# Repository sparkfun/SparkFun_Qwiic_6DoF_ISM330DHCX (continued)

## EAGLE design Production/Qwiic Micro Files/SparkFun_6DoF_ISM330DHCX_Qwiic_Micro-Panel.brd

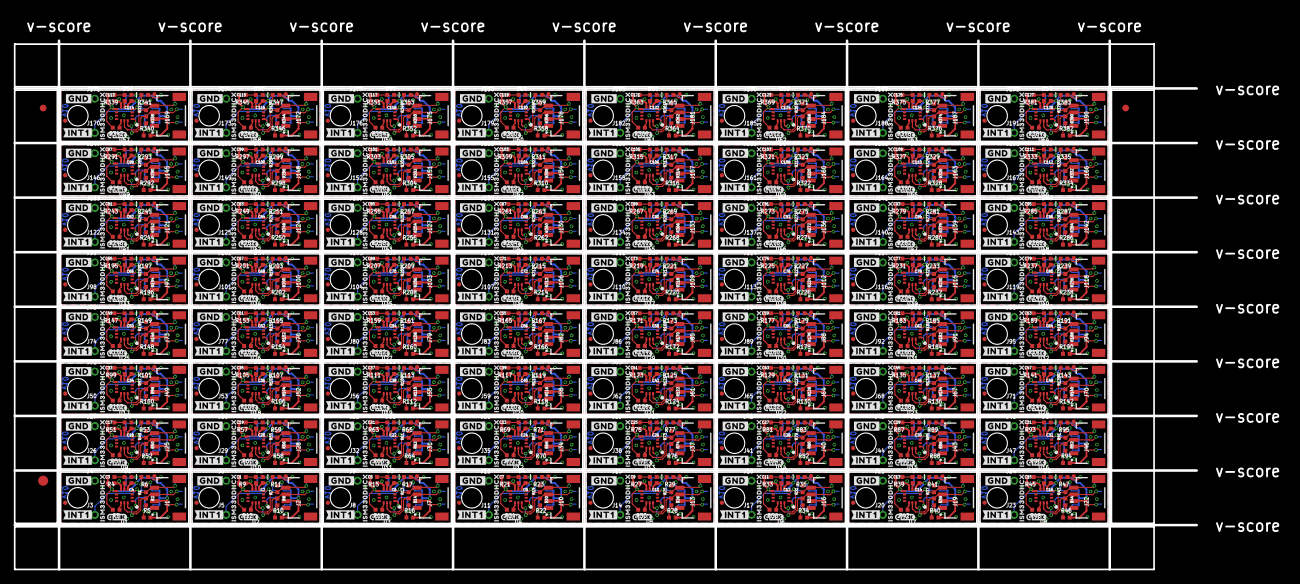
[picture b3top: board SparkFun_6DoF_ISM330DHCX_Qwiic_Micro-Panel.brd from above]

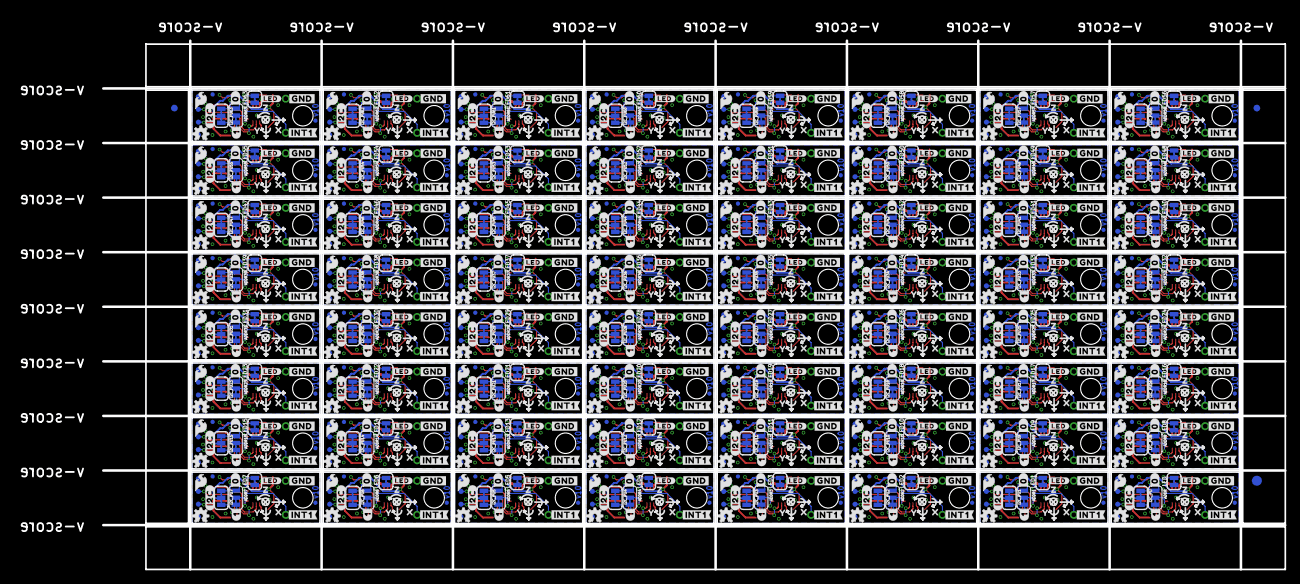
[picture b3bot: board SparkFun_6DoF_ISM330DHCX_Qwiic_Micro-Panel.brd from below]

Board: 2 copper layers, 176.0 x 78.7 mm, 2630 parts (1283 on the bottom side), 832 nets.

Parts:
ADDR, ADDR1, ADDR2, ADDR3, ADDR4, ADDR5, ADDR6, ADDR7, ADDR8, ADDR9, ADDR10, ADDR11, ADDR12, ADDR13, ADDR14, ADDR15, ADDR16, ADDR17, ADDR18, ADDR19, ADDR20, ADDR21, ADDR22, ADDR23, ADDR24, ADDR25, ADDR26, ADDR27, ADDR28, ADDR29, ADDR30, ADDR31, ADDR32, ADDR33, ADDR34, ADDR35, ADDR36, ADDR37, ADDR38, ADDR39, ADDR40, ADDR41, ADDR42, ADDR43, ADDR44, ADDR45, ADDR46, ADDR47, ADDR48, ADDR49, ADDR50, ADDR51, ADDR52, ADDR53, ADDR54, ADDR55, ADDR56, ADDR57, ADDR58, ADDR59, ADDR60, ADDR61, ADDR62, ADDR63: JUMPER-SMT_3_1-NC_TRACE_SILK; SMT-JUMPER_3_1-NC_TRACE_SILK
C1, C2, C3, C4, C5, C6, C7, C8, C9, C10, C11, C12, C13, C14, C15, C16, C17, C18, C19, C20, C21, C22, C23, C24, C25, C26, C27, C28, C29, C30, C31, C32, C33, C34, C35, C36, C37, C38, C39, C40, C41, C42, C43, C44, C45, C46, C47, C48, C49, C50, C51, C52, C53, C54, C55, C56, C57, C58, C59, C60, C61, C62, C63, C64, C65, C66, C67, C68, C69, C70, C71, C72, C73, C74, C75, C76, C77, C78, C79, C80, C81, C82, C83, C84, C85, C86, C87, C88, C89, C90, C91, C92, C93, C94, C95, C96, C97, C98, C99, C100, C101, C102, C103, C104, C105, C106, C107, C108, C109, C110, C111, C112, C113, C114, C115, C116, C117, C118, C119, C120, C121, C122, C123, C124, C125, C126, C127, C128: 0.1uF; 0402-TIGHT
D1, D2, D3, D4, D5, D6, D7, D8, D9, D10, D11, D12, D13, D14, D15, D16, D17, D18, D19, D20, D21, D22, D23, D24, D25, D26, D27, D28, D29, D30, D31, D32, D33, D34, D35, D36, D37, D38, D39, D40, D41, D42, D43, D44, D45, D46, D47, D48, D49, D50, D51, D52, D53, D54, D55, D56, D57, D58, D59, D60, D61, D62, D63, D64: RED; 0402-TIGHT
E$1, E$2, E$3, E$4: FIDUCIAL-1X2
E$5, E$6: FIDUCIAL-1.5X3
FD1, FD2, FD3, FD4, FD5, FD6, FD7, FD8, FD9, FD10, FD11, FD12, FD13, FD14, FD15, FD16, FD17, FD18, FD19, FD20, FD21, FD22, FD23, FD24, FD25, FD26, FD27, FD28, FD29, FD30, FD31, FD32, FD33, FD34, FD35, FD36, FD37, FD38, FD39, FD40, FD41, FD42, FD43, FD44, FD45, FD46, FD47, FD48, FD49, FD50, FD51, FD52, FD53, FD54, FD55, FD56, FD57, FD58, FD59, FD60, FD61, FD62, FD63, FD64, FD65, FD66, FD67, FD68, FD69, FD70, FD71, FD72, FD73, FD74, FD75, FD76, FD77, FD78, FD79, FD80, FD81, FD82, FD83, FD84, FD85, FD86, FD87, FD88, FD89, FD90, FD91, FD92, FD93, FD94, FD95, FD96, FD97, FD98, FD99, FD100, FD101, FD102, FD103, FD104, FD105, FD106, FD107, FD108, FD109, FD110, FD111, FD112, FD113, FD114, FD115, FD116, FD117, FD118, FD119, FD120, FD121, FD122, FD123, FD124, FD125, FD126, FD127, FD128: FIDUCIALUFIDUCIAL; FIDUCIAL-MICRO
FID1, FID2, FID3, FID4, FID5, FID6, FID7, FID8, FID9, FID10, FID11, FID12, FID13, FID14, FID15, FID16, FID17, FID18, FID19, FID20, FID21, FID22, FID23, FID24, FID25, FID26, FID27, FID28, FID29, FID30, FID31, FID32, FID33, FID34, FID35, FID36, FID37, FID38, FID39, FID40, FID41, FID42, FID43, FID44, FID45, FID46, FID47, FID48, FID49, FID50, FID51, FID52, FID53, FID54, FID55, FID56, FID57, FID58, FID59, FID60, FID61, FID62, FID63, FID64, FID65, FID66, FID67, FID68, FID69, FID70, FID71, FID72, FID73, FID74, FID75, FID76, FID77, FID78, FID79, FID80, FID81, FID82, FID83, FID84, FID85, FID86, FID87, FID88, FID89, FID90, FID91, FID92, FID93, FID94, FID95, FID96, FID97, FID98, FID99, FID100, FID101, FID102, FID103, FID104, FID105, FID106, FID107, FID108, FID109, FID110, FID111, FID112, FID113, FID114, FID115, FID116, FID117, FID118, FID119, FID120, FID121, FID122, FID123, FID124, FID125, FID126, FID127, FID128: FIDUCIALUFIDUCIAL; FIDUCIAL-MICRO
I2C_PU, I2C_PU1, I2C_PU2, I2C_PU3, I2C_PU4, I2C_PU5, I2C_PU6, I2C_PU7, I2C_PU8, I2C_PU9, I2C_PU10, I2C_PU11, I2C_PU12, I2C_PU13, I2C_PU14, I2C_PU15, I2C_PU16, I2C_PU17, I2C_PU18, I2C_PU19, I2C_PU20, I2C_PU21, I2C_PU22, I2C_PU23, I2C_PU24, I2C_PU25, I2C_PU26, I2C_PU27, I2C_PU28, I2C_PU29, I2C_PU30, I2C_PU31, I2C_PU32, I2C_PU33, I2C_PU34, I2C_PU35, I2C_PU36, I2C_PU37, I2C_PU38, I2C_PU39, I2C_PU40, I2C_PU41, I2C_PU42, I2C_PU43, I2C_PU44, I2C_PU45, I2C_PU46, I2C_PU47, I2C_PU48, I2C_PU49, I2C_PU50, I2C_PU51, I2C_PU52, I2C_PU53, I2C_PU54, I2C_PU55, I2C_PU56, I2C_PU57, I2C_PU58, I2C_PU59, I2C_PU60, I2C_PU61, I2C_PU62, I2C_PU63: S_MODE; SMT-JUMPER_3_2-NC_TRACE_SILK
J1, J2, J7, J10, J13, J16, J19, J22, J25, J28, J31, J34, J37, J40, J43, J46, J49, J52, J55, J58, J61, J64, J67, J70, J73, J76, J79, J82, J85, J88, J91, J94, J97, J100, J103, J106, J109, J112, J115, J118, J121, J124, J127, J130, J133, J136, J139, J142, J145, J148, J151, J154, J157, J160, J163, J166, J169, J172, J175, J178, J181, J184, J187, J190: Qwiic Right Angle; JST04_1MM_RA
J3, J4, J5, J6, J8, J9, J11, J12, J14, J15, J17, J18, J20, J21, J23, J24, J26, J27, J29, J30, J32, J33, J35, J36, J38, J39, J41, J42, J44, J45, J47, J48, J50, J51, J53, J54, J56, J57, J59, J60, J62, J63, J65, J66, J68, J69, J71, J72, J74, J75, J77, J78, J80, J81, J83, J84, J86, J87, J89, J90, J92, J93, J95, J96, J98, J99, J101, J102, J104, J105, J107, J108, J110, J111, J113, J114, J116, J117, J119, J120, J122, J123, J125, J126, J128, J129, J131, J132, J134, J135, J137, J138, J140, J141, J143, J144, J146, J147, J149, J150, J152, J153, J155, J156, J158, J159, J161, J162, J164, J165, J167, J168, J170, J171, J173, J174, J176, J177, J179, J180, J182, J183, J185, J186, J188, J189, J191, J192: 1X01_1MM_NO_SILK
LED, LED1, LED2, LED3, LED4, LED5, LED6, LED7, LED8, LED9, LED10, LED11, LED12, LED13, LED14, LED15, LED16, LED17, LED18, LED19, LED20, LED21, LED22, LED23, LED24, LED25, LED26, LED27, LED28, LED29, LED30, LED31, LED32, LED33, LED34, LED35, LED36, LED37, LED38, LED39, LED40, LED41, LED42, LED43, LED44, LED45, LED46, LED47, LED48, LED49, LED50, LED51, LED52, LED53, LED54, LED55, LED56, LED57, LED58, LED59, LED60, LED61, LED62, LED63: JUMPER-SMT_2_NC_TRACE_SILK; SMT-JUMPER_2_NC_TRACE_SILK
LOGO1, LOGO5, LOGO8, LOGO11, LOGO14, LOGO17, LOGO20, LOGO23, LOGO26, LOGO29, LOGO32, LOGO35, LOGO38, LOGO41, LOGO44, LOGO47, LOGO50, LOGO53, LOGO56, LOGO59, LOGO62, LOGO65, LOGO68, LOGO71, LOGO74, LOGO77, LOGO80, LOGO83, LOGO86, LOGO89, LOGO92, LOGO95, LOGO98, LOGO101, LOGO104, LOGO107, LOGO110, LOGO113, LOGO116, LOGO119, LOGO122, LOGO125, LOGO128, LOGO131, LOGO134, LOGO137, LOGO140, LOGO143, LOGO146, LOGO149, LOGO152, LOGO155, LOGO158, LOGO161, LOGO164, LOGO167, LOGO170, LOGO173, LOGO176, LOGO179, LOGO182, LOGO185, LOGO188, LOGO191: QWIIC_LOGO_3MM; QWIIC_3MM
LOGO2, LOGO4, LOGO7, LOGO10, LOGO13, LOGO16, LOGO19, LOGO22, LOGO25, LOGO28, LOGO31, LOGO34, LOGO37, LOGO40, LOGO43, LOGO46, LOGO49, LOGO52, LOGO55, LOGO58, LOGO61, LOGO64, LOGO67, LOGO70, LOGO73, LOGO76, LOGO79, LOGO82, LOGO85, LOGO88, LOGO91, LOGO94, LOGO97, LOGO100, LOGO103, LOGO106, LOGO109, LOGO112, LOGO115, LOGO118, LOGO121, LOGO124, LOGO127, LOGO130, LOGO133, LOGO136, LOGO139, LOGO142, LOGO145, LOGO148, LOGO151, LOGO154, LOGO157, LOGO160, LOGO163, LOGO166, LOGO169, LOGO172, LOGO175, LOGO178, LOGO181, LOGO184, LOGO187, LOGO190: OSHW-LOGOMINI; OSHW-LOGO-MINI
LOGO3, LOGO6, LOGO9, LOGO12, LOGO15, LOGO18, LOGO21, LOGO24, LOGO27, LOGO30, LOGO33, LOGO36, LOGO39, LOGO42, LOGO45, LOGO48, LOGO51, LOGO54, LOGO57, LOGO60, LOGO63, LOGO66, LOGO69, LOGO72, LOGO75, LOGO78, LOGO81, LOGO84, LOGO87, LOGO90, LOGO93, LOGO96, LOGO99, LOGO102, LOGO105, LOGO108, LOGO111, LOGO114, LOGO117, LOGO120, LOGO123, LOGO126, LOGO129, LOGO132, LOGO135, LOGO138, LOGO141, LOGO144, LOGO147, LOGO150, LOGO153, LOGO156, LOGO159, LOGO162, LOGO165, LOGO168, LOGO171, LOGO174, LOGO177, LOGO180, LOGO183, LOGO186, LOGO189, LOGO192: SFE_LOGO_NAME_FLAMEBLANK; BLANK
R1, R2, R7, R8, R13, R14, R19, R20, R25, R26, R31, R32, R37, R38, R43, R44, R49, R50, R55, R56, R61, R62, R67, R68, R73, R74, R79, R80, R85, R86, R91, R92, R97, R98, R103, R104, R109, R110, R115, R116, R121, R122, R127, R128, R133, R134, R139, R140, R145, R146, R151, R152, R157, R158, R163, R164, R169, R170, R175, R176, R181, R182, R187, R188, R193, R194, R199, R200, R205, R206, R211, R212, R217, R218, R223, R224, R229, R230, R235, R236, R241, R242, R247, R248, R253, R254, R259, R260, R265, R266, R271, R272, R277, R278, R283, R284, R289, R290, R295, R296, R301, R302, R307, R308, R313, R314, R319, R320, R325, R326, R331, R332, R337, R338, R343, R344, R349, R350, R355, R356, R361, R362, R367, R368, R373, R374, R379, R380: 2.2k; 0402-TIGHT
R3, R5, R6, R10, R11, R12, R16, R17, R18, R22, R23, R24, R28, R29, R30, R34, R35, R36, R40, R41, R42, R46, R47, R48, R52, R53, R54, R58, R59, R60, R64, R65, R66, R70, R71, R72, R76, R77, R78, R82, R83, R84, R88, R89, R90, R94, R95, R96, R100, R101, R102, R106, R107, R108, R112, R113, R114, R118, R119, R120, R124, R125, R126, R130, R131, R132, R136, R137, R138, R142, R143, R144, R148, R149, R150, R154, R155, R156, R160, R161, R162, R166, R167, R168, R172, R173, R174, R178, R179, R180, R184, R185, R186, R190, R191, R192, R196, R197, R198, R202, R203, R204, R208, R209, R210, R214, R215, R216, R220, R221, R222, R226, R227, R228, R232, R233, R234, R238, R239, R240, R244, R245, R246, R250, R251, R252, R256, R257, R258, R262, R263, R264, R268, R269, R270, R274, R275, R276, R280, R281, R282, R286, R287, R288, R292, R293, R294, R298, R299, R300, R304, R305, R306, R310, R311, R312, R316, R317, R318, R322, R323, R324, R328, R329, R330, R334, R335, R336, R340, R341, R342, R346, R347, R348, R352, R353, R354, R358, R359, R360, R364, R365, R366, R370, R371, R372, R376, R377, R378, R382, R383, R384: 10k; 0402-TIGHT
R4, R9, R15, R21, R27, R33, R39, R45, R51, R57, R63, R69, R75, R81, R87, R93, R99, R105, R111, R117, R123, R129, R135, R141, R147, R153, R159, R165, R171, R177, R183, R189, R195, R201, R207, R213, R219, R225, R231, R237, R243, R249, R255, R261, R267, R273, R279, R285, R291, R297, R303, R309, R315, R321, R327, R333, R339, R345, R351, R357, R363, R369, R375, R381: 1k; 0402-TIGHT
STANDOFF1, STANDOFF2, STANDOFF3, STANDOFF4, STANDOFF5, STANDOFF6, STANDOFF7, STANDOFF8, STANDOFF9, STANDOFF10, STANDOFF11, STANDOFF12, STANDOFF13, STANDOFF14, STANDOFF15, STANDOFF16, STANDOFF17, STANDOFF18, STANDOFF19, STANDOFF20, STANDOFF21, STANDOFF22, STANDOFF23, STANDOFF24, STANDOFF25, STANDOFF26, STANDOFF27, STANDOFF28, STANDOFF29, STANDOFF30, STANDOFF31, STANDOFF32, STANDOFF33, STANDOFF34, STANDOFF35, STANDOFF36, STANDOFF37, STANDOFF38, STANDOFF39, STANDOFF40, STANDOFF41, STANDOFF42, STANDOFF43, STANDOFF44, STANDOFF45, STANDOFF46, STANDOFF47, STANDOFF48, STANDOFF49, STANDOFF50, STANDOFF51, STANDOFF52, STANDOFF53, STANDOFF54, STANDOFF55, STANDOFF56, STANDOFF57, STANDOFF58, STANDOFF59, STANDOFF60, STANDOFF61, STANDOFF62, STANDOFF63, STANDOFF64: STAND-OFFTIGHT; STAND-OFF-TIGHT
TP1, TP2, TP3, TP4, TP5, TP6, TP7, TP8, TP9, TP10, TP11, TP12, TP13, TP14, TP15, TP16, TP17, TP18, TP19, TP20, TP21, TP22, TP23, TP24, TP25, TP26, TP27, TP28, TP29, TP30, TP31, TP32, TP33, TP34, TP35, TP36, TP37, TP38, TP39, TP40, TP41, TP42, TP43, TP44, TP45, TP46, TP47, TP48, TP49, TP50, TP51, TP52, TP53, TP54, TP55, TP56, TP57, TP58, TP59, TP60, TP61, TP62, TP63, TP64, TP65, TP66, TP67, TP68, TP69, TP70, TP71, TP72, TP73, TP74, TP75, TP76, TP77, TP78, TP79, TP80, TP81, TP82, TP83, TP84, TP85, TP86, TP87, TP88, TP89, TP90, TP91, TP92, TP93, TP94, TP95, TP96, TP97, TP98, TP99, TP100, TP101, TP102, TP103, TP104, TP105, TP106, TP107, TP108, TP109, TP110, TP111, TP112, TP113, TP114, TP115, TP116, TP117, TP118, TP119, TP120, TP121, TP122, TP123, TP124, TP125, TP126, TP127, TP128, TP129, TP130, TP131, TP132, TP133, TP134, TP135, TP136, TP137, TP138, TP139, TP140, TP141, TP142, TP143, TP144, TP145, TP146, TP147, TP148, TP149, TP150, TP151, TP152, TP153, TP154, TP155, TP156, TP157, TP158, TP159, TP160, TP161, TP162, TP163, TP164, TP165, TP166, TP167, TP168, TP169, TP170, TP171, TP172, TP173, TP174, TP175, TP176, TP177, TP178, TP179, TP180, TP181, TP182, TP183, TP184, TP185, TP186, TP187, TP188, TP189, TP190, TP191, TP192, TP193, TP194, TP195, TP196, TP197, TP198, TP199, TP200, TP201, TP202, TP203, TP204, TP205, TP206, TP207, TP208, TP209, TP210, TP211, TP212, TP213, TP214, TP215, TP216, TP217, TP218, TP219, TP220, TP221, TP222, TP223, TP224, TP225, TP226, TP227, TP228, TP229, TP230, TP231, TP232, TP233, TP234, TP235, TP236, TP237, TP238, TP239, TP240, TP241, TP242, TP243, TP244, TP245, TP246, TP247, TP248, TP249, TP250, TP251, TP252, TP253, TP254, TP255, TP256: TEST-POINT3; PAD.03X.03
U1, U2, U3, U4, U5, U6, U7, U8, U9, U10, U11, U12, U13, U14, U15, U16, U17, U18, U19, U20, U21, U22, U23, U24, U25, U26, U27, U28, U29, U30, U31, U32, U33, U34, U35, U36, U37, U38, U39, U40, U41, U42, U43, U44, U45, U46, U47, U48, U49, U50, U51, U52, U53, U54, U55, U56, U57, U58, U59, U60, U61, U62, U63, U64: ISM330DHCX; LGA-14L
U$1, U$19, U$33, U$46, U$59, U$72, U$85, U$98, U$111, U$124, U$137, U$150, U$163, U$176, U$189, U$202, U$215, U$228, U$241, U$254, U$267, U$280, U$293, U$306, U$319, U$332, U$345, U$358, U$371, U$384, U$397, U$410, U$423, U$436, U$449, U$462, U$475, U$488, U$501, U$514, U$527, U$540, U$553, U$566, U$579, U$592, U$605, U$618, U$631, U$644, U$657, U$670, U$683, U$696, U$709, U$722, U$735, U$748, U$761, U$774, U$787, U$800, U$813, U$826: #0#4
U$2, U$20, U$34, U$47, U$60, U$73, U$86, U$99, U$112, U$125, U$138, U$151, U$164, U$177, U$190, U$203, U$216, U$229, U$242, U$255, U$268, U$281, U$294, U$307, U$320, U$333, U$346, U$359, U$372, U$385, U$398, U$411, U$424, U$437, U$450, U$463, U$476, U$489, U$502, U$515, U$528, U$541, U$554, U$567, U$580, U$593, U$606, U$619, U$632, U$645, U$658, U$671, U$684, U$697, U$710, U$723, U$736, U$749, U$762, U$775, U$788, U$801, U$814, U$827: #1#4
U$3, U$17, U$31, U$44, U$57, U$70, U$83, U$96, U$109, U$122, U$135, U$148, U$161, U$174, U$187, U$200, U$213, U$226, U$239, U$252, U$265, U$278, U$291, U$304, U$317, U$330, U$343, U$356, U$369, U$382, U$395, U$408, U$421, U$434, U$447, U$460, U$473, U$486, U$499, U$512, U$525, U$538, U$551, U$564, U$577, U$590, U$603, U$616, U$629, U$642, U$655, U$668, U$681, U$694, U$707, U$720, U$733, U$746, U$759, U$772, U$785, U$798, U$811, U$824: #LED#2121
U$4, U$10, U$22, U$23, U$36, U$37, U$49, U$50, U$62, U$63, U$75, U$76, U$88, U$89, U$101, U$102, U$114, U$115, U$127, U$128, U$140, U$141, U$153, U$154, U$166, U$167, U$179, U$180, U$192, U$193, U$205, U$206, U$218, U$219, U$231, U$232, U$244, U$245, U$257, U$258, U$270, U$271, U$283, U$284, U$296, U$297, U$309, U$310, U$322, U$323, U$335, U$336, U$348, U$349, U$361, U$362, U$374, U$375, U$387, U$388, U$400, U$401, U$413, U$414, U$426, U$427, U$439, U$440, U$452, U$453, U$465, U$466, U$478, U$479, U$491, U$492, U$504, U$505, U$517, U$518, U$530, U$531, U$543, U$544, U$556, U$557, U$569, U$570, U$582, U$583, U$595, U$596, U$608, U$609, U$621, U$622, U$634, U$635, U$647, U$648, U$660, U$661, U$673, U$674, U$686, U$687, U$699, U$700, U$712, U$713, U$725, U$726, U$738, U$739, U$751, U$752, U$764, U$765, U$777, U$778, U$790, U$791, U$803, U$804, U$816, U$817, U$829, U$830: #GND#4
U$5, U$24, U$38, U$51, U$64, U$77, U$90, U$103, U$116, U$129, U$142, U$155, U$168, U$181, U$194, U$207, U$220, U$233, U$246, U$259, U$272, U$285, U$298, U$311, U$324, U$337, U$350, U$363, U$376, U$389, U$402, U$415, U$428, U$441, U$454, U$467, U$480, U$493, U$506, U$519, U$532, U$545, U$558, U$571, U$584, U$597, U$610, U$623, U$636, U$649, U$662, U$675, U$688, U$701, U$714, U$727, U$740, U$753, U$766, U$779, U$792, U$805, U$818, U$831: #INT1#0
U$6, U$18, U$32, U$45, U$58, U$71, U$84, U$97, U$110, U$123, U$136, U$149, U$162, U$175, U$188, U$201, U$214, U$227, U$240, U$253, U$266, U$279, U$292, U$305, U$318, U$331, U$344, U$357, U$370, U$383, U$396, U$409, U$422, U$435, U$448, U$461, U$474, U$487, U$500, U$513, U$526, U$539, U$552, U$565, U$578, U$591, U$604, U$617, U$630, U$643, U$656, U$669, U$682, U$695, U$708, U$721, U$734, U$747, U$760, U$773, U$786, U$799, U$812, U$825: ISM330DHCX2120
U$7, U$14, U$27, U$41, U$54, U$67, U$80, U$93, U$106, U$119, U$132, U$145, U$158, U$171, U$184, U$197, U$210, U$223, U$236, U$249, U$262, U$275, U$288, U$301, U$314, U$327, U$340, U$353, U$366, U$379, U$392, U$405, U$418, U$431, U$444, U$457, U$470, U$483, U$496, U$509, U$522, U$535, U$548, U$561, U$574, U$587, U$600, U$613, U$626, U$639, U$652, U$665, U$678, U$691, U$704, U$717, U$730, U$743, U$756, U$769, U$782, U$795, U$808, U$821: X2114
U$8, U$15, U$28, U$42, U$55, U$68, U$81, U$94, U$107, U$120, U$133, U$146, U$159, U$172, U$185, U$198, U$211, U$224, U$237, U$250, U$263, U$276, U$289, U$302, U$315, U$328, U$341, U$354, U$367, U$380, U$393, U$406, U$419, U$432, U$445, U$458, U$471, U$484, U$497, U$510, U$523, U$536, U$549, U$562, U$575, U$588, U$601, U$614, U$627, U$640, U$653, U$666, U$679, U$692, U$705, U$718, U$731, U$744, U$757, U$770, U$783, U$796, U$809, U$822: Y2115
U$9, U$16, U$30, U$43, U$56, U$69, U$82, U$95, U$108, U$121, U$134, U$147, U$160, U$173, U$186, U$199, U$212, U$225, U$238, U$251, U$264, U$277, U$290, U$303, U$316, U$329, U$342, U$355, U$368, U$381, U$394, U$407, U$420, U$433, U$446, U$459, U$472, U$485, U$498, U$511, U$524, U$537, U$550, U$563, U$576, U$589, U$602, U$615, U$628, U$641, U$654, U$667, U$680, U$693, U$706, U$719, U$732, U$745, U$758, U$771, U$784, U$797, U$810, U$823: Z2116
U$11, U$25, U$39, U$52, U$65, U$78, U$91, U$104, U$117, U$130, U$143, U$156, U$169, U$182, U$195, U$208, U$221, U$234, U$247, U$260, U$273, U$286, U$299, U$312, U$325, U$338, U$351, U$364, U$377, U$390, U$403, U$416, U$429, U$442, U$455, U$468, U$481, U$494, U$507, U$520, U$533, U$546, U$559, U$572, U$585, U$598, U$611, U$624, U$637, U$650, U$663, U$676, U$689, U$702, U$715, U$728, U$741, U$754, U$767, U$780, U$793, U$806, U$819, U$832: #INT1#2
U$12, U$21, U$35, U$48, U$61, U$74, U$87, U$100, U$113, U$126, U$139, U$152, U$165, U$178, U$191, U$204, U$217, U$230, U$243, U$256, U$269, U$282, U$295, U$308, U$321, U$334, U$347, U$360, U$373, U$386, U$399, U$412, U$425, U$438, U$451, U$464, U$477, U$490, U$503, U$516, U$529, U$542, U$555, U$568, U$581, U$594, U$607, U$620, U$633, U$646, U$659, U$672, U$685, U$698, U$711, U$724, U$737, U$750, U$763, U$776, U$789, U$802, U$815, U$828: #I2C#4
U$13, U$26, U$29, U$40, U$53, U$66, U$79, U$92, U$105, U$118, U$131, U$144, U$157, U$170, U$183, U$196, U$209, U$222, U$235, U$248, U$261, U$274, U$287, U$300, U$313, U$326, U$339, U$352, U$365, U$378, U$391, U$404, U$417, U$430, U$443, U$456, U$469, U$482, U$495, U$508, U$521, U$534, U$547, U$560, U$573, U$586, U$599, U$612, U$625, U$638, U$651, U$664, U$677, U$690, U$703, U$716, U$729, U$742, U$755, U$768, U$781, U$794, U$807, U$820: SFE_LOGO_FLAME_.1

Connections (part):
3.3V: C3.1, C4.1, I2C_PU.2, J1.2, R3.2, R4.2, R5.2, TP3.1, U1.P5, U1.P8
3.3V1: C1.1, C2.1, I2C_PU1.2, J2.2, R9.2, R10.2, R12.2, TP7.1, U2.P5, U2.P8
3.3V2: C5.1, C6.1, I2C_PU2.2, J7.2, R15.2, R16.2, R18.2, TP11.1, U3.P5, U3.P8
3.3V3: C7.1, C8.1, I2C_PU3.2, J10.2, R21.2, R22.2, R24.2, TP15.1, U4.P5, U4.P8
3.3V4: C9.1, C10.1, I2C_PU4.2, J13.2, R27.2, R28.2, R30.2, TP19.1, U5.P5, U5.P8
3.3V5: C11.1, C12.1, I2C_PU5.2, J16.2, R33.2, R34.2, R36.2, TP23.1, U6.P5, U6.P8
3.3V6: C13.1, C14.1, I2C_PU6.2, J19.2, R39.2, R40.2, R42.2, TP27.1, U7.P5, U7.P8
3.3V7: C15.1, C16.1, I2C_PU7.2, J22.2, R45.2, R46.2, R48.2, TP31.1, U8.P5, U8.P8
3.3V8: C17.1, C18.1, I2C_PU8.2, J25.2, R51.2, R52.2, R54.2, TP35.1, U9.P5, U9.P8
3.3V9: C19.1, C20.1, I2C_PU9.2, J28.2, R57.2, R58.2, R60.2, TP39.1, U10.P5, U10.P8
3.3V10: C21.1, C22.1, I2C_PU10.2, J31.2, R63.2, R64.2, R66.2, TP43.1, U11.P5, U11.P8
3.3V11: C23.1, C24.1, I2C_PU11.2, J34.2, R69.2, R70.2, R72.2, TP47.1, U12.P5, U12.P8
3.3V12: C25.1, C26.1, I2C_PU12.2, J37.2, R75.2, R76.2, R78.2, TP51.1, U13.P5, U13.P8
3.3V13: C27.1, C28.1, I2C_PU13.2, J40.2, R81.2, R82.2, R84.2, TP55.1, U14.P5, U14.P8
3.3V14: C29.1, C30.1, I2C_PU14.2, J43.2, R87.2, R88.2, R90.2, TP59.1, U15.P5, U15.P8
3.3V15: C31.1, C32.1, I2C_PU15.2, J46.2, R93.2, R94.2, R96.2, TP63.1, U16.P5, U16.P8
3.3V16: C33.1, C34.1, I2C_PU16.2, J49.2, R99.2, R100.2, R102.2, TP67.1, U17.P5, U17.P8
3.3V17: C35.1, C36.1, I2C_PU17.2, J52.2, R105.2, R106.2, R108.2, TP71.1, U18.P5, U18.P8
3.3V18: C37.1, C38.1, I2C_PU18.2, J55.2, R111.2, R112.2, R114.2, TP75.1, U19.P5, U19.P8
3.3V19: C39.1, C40.1, I2C_PU19.2, J58.2, R117.2, R118.2, R120.2, TP79.1, U20.P5, U20.P8
3.3V20: C41.1, C42.1, I2C_PU20.2, J61.2, R123.2, R124.2, R126.2, TP83.1, U21.P5, U21.P8
3.3V21: C43.1, C44.1, I2C_PU21.2, J64.2, R129.2, R130.2, R132.2, TP87.1, U22.P5, U22.P8
3.3V22: C45.1, C46.1, I2C_PU22.2, J67.2, R135.2, R136.2, R138.2, TP91.1, U23.P5, U23.P8
3.3V23: C47.1, C48.1, I2C_PU23.2, J70.2, R141.2, R142.2, R144.2, TP95.1, U24.P5, U24.P8
3.3V24: C49.1, C50.1, I2C_PU24.2, J73.2, R147.2, R148.2, R150.2, TP99.1, U25.P5, U25.P8
3.3V25: C51.1, C52.1, I2C_PU25.2, J76.2, R153.2, R154.2, R156.2, TP103.1, U26.P5, U26.P8
3.3V26: C53.1, C54.1, I2C_PU26.2, J79.2, R159.2, R160.2, R162.2, TP107.1, U27.P5, U27.P8
3.3V27: C55.1, C56.1, I2C_PU27.2, J82.2, R165.2, R166.2, R168.2, TP111.1, U28.P5, U28.P8
3.3V28: C57.1, C58.1, I2C_PU28.2, J85.2, R171.2, R172.2, R174.2, TP115.1, U29.P5, U29.P8
3.3V29: C59.1, C60.1, I2C_PU29.2, J88.2, R177.2, R178.2, R180.2, TP119.1, U30.P5, U30.P8
3.3V30: C61.1, C62.1, I2C_PU30.2, J91.2, R183.2, R184.2, R186.2, TP123.1, U31.P5, U31.P8
3.3V31: C63.1, C64.1, I2C_PU31.2, J94.2, R189.2, R190.2, R192.2, TP127.1, U32.P5, U32.P8
3.3V32: C65.1, C66.1, I2C_PU32.2, J97.2, R195.2, R196.2, R198.2, TP131.1, U33.P5, U33.P8
3.3V33: C67.1, C68.1, I2C_PU33.2, J100.2, R201.2, R202.2, R204.2, TP135.1, U34.P5, U34.P8
3.3V34: C69.1, C70.1, I2C_PU34.2, J103.2, R207.2, R208.2, R210.2, TP139.1, U35.P5, U35.P8
3.3V35: C71.1, C72.1, I2C_PU35.2, J106.2, R213.2, R214.2, R216.2, TP143.1, U36.P5, U36.P8
3.3V36: C73.1, C74.1, I2C_PU36.2, J109.2, R219.2, R220.2, R222.2, TP147.1, U37.P5, U37.P8
3.3V37: C75.1, C76.1, I2C_PU37.2, J112.2, R225.2, R226.2, R228.2, TP151.1, U38.P5, U38.P8
3.3V38: C77.1, C78.1, I2C_PU38.2, J115.2, R231.2, R232.2, R234.2, TP155.1, U39.P5, U39.P8
3.3V39: C79.1, C80.1, I2C_PU39.2, J118.2, R237.2, R238.2, R240.2, TP159.1, U40.P5, U40.P8
3.3V40: C81.1, C82.1, I2C_PU40.2, J121.2, R243.2, R244.2, R246.2, TP163.1, U41.P5, U41.P8
3.3V41: C83.1, C84.1, I2C_PU41.2, J124.2, R249.2, R250.2, R252.2, TP167.1, U42.P5, U42.P8
3.3V42: C85.1, C86.1, I2C_PU42.2, J127.2, R255.2, R256.2, R258.2, TP171.1, U43.P5, U43.P8
3.3V43: C87.1, C88.1, I2C_PU43.2, J130.2, R261.2, R262.2, R264.2, TP175.1, U44.P5, U44.P8
3.3V44: C89.1, C90.1, I2C_PU44.2, J133.2, R267.2, R268.2, R270.2, TP179.1, U45.P5, U45.P8
3.3V45: C91.1, C92.1, I2C_PU45.2, J136.2, R273.2, R274.2, R276.2, TP183.1, U46.P5, U46.P8
3.3V46: C93.1, C94.1, I2C_PU46.2, J139.2, R279.2, R280.2, R282.2, TP187.1, U47.P5, U47.P8
3.3V47: C95.1, C96.1, I2C_PU47.2, J142.2, R285.2, R286.2, R288.2, TP191.1, U48.P5, U48.P8
3.3V48: C97.1, C98.1, I2C_PU48.2, J145.2, R291.2, R292.2, R294.2, TP195.1, U49.P5, U49.P8
3.3V49: C99.1, C100.1, I2C_PU49.2, J148.2, R297.2, R298.2, R300.2, TP199.1, U50.P5, U50.P8
3.3V50: C101.1, C102.1, I2C_PU50.2, J151.2, R303.2, R304.2, R306.2, TP203.1, U51.P5, U51.P8
3.3V51: C103.1, C104.1, I2C_PU51.2, J154.2, R309.2, R310.2, R312.2, TP207.1, U52.P5, U52.P8
3.3V52: C105.1, C106.1, I2C_PU52.2, J157.2, R315.2, R316.2, R318.2, TP211.1, U53.P5, U53.P8
3.3V53: C107.1, C108.1, I2C_PU53.2, J160.2, R321.2, R322.2, R324.2, TP215.1, U54.P5, U54.P8
3.3V54: C109.1, C110.1, I2C_PU54.2, J163.2, R327.2, R328.2, R330.2, TP219.1, U55.P5, U55.P8
3.3V55: C111.1, C112.1, I2C_PU55.2, J166.2, R333.2, R334.2, R336.2, TP223.1, U56.P5, U56.P8
3.3V56: C113.1, C114.1, I2C_PU56.2, J169.2, R339.2, R340.2, R342.2, TP227.1, U57.P5, U57.P8
3.3V57: C115.1, C116.1, I2C_PU57.2, J172.2, R345.2, R346.2, R348.2, TP231.1, U58.P5, U58.P8
3.3V58: C117.1, C118.1, I2C_PU58.2, J175.2, R351.2, R352.2, R354.2, TP235.1, U59.P5, U59.P8
3.3V59: C119.1, C120.1, I2C_PU59.2, J178.2, R357.2, R358.2, R360.2, TP239.1, U60.P5, U60.P8
3.3V60: C121.1, C122.1, I2C_PU60.2, J181.2, R363.2, R364.2, R366.2, TP243.1, U61.P5, U61.P8
3.3V61: C123.1, C124.1, I2C_PU61.2, J184.2, R369.2, R370.2, R372.2, TP247.1, U62.P5, U62.P8
3.3V62: C125.1, C126.1, I2C_PU62.2, J187.2, R375.2, R376.2, R378.2, TP251.1, U63.P5, U63.P8
3.3V63: C127.1, C128.1, I2C_PU63.2, J190.2, R381.2, R382.2, R384.2, TP255.1, U64.P5, U64.P8
GND: C3.2, C4.2, J1.1, J4.1, LED.1, R6.1, TP4.1, U1.P6, U1.P7
GND1: C1.2, C2.2, J2.1, J6.1, LED1.1, R11.1, TP8.1, U2.P6, U2.P7
GND2: C5.2, C6.2, J7.1, J9.1, LED2.1, R17.1, TP12.1, U3.P6, U3.P7
GND3: C7.2, C8.2, J10.1, J12.1, LED3.1, R23.1, TP16.1, U4.P6, U4.P7
GND4: C9.2, C10.2, J13.1, J15.1, LED4.1, R29.1, TP20.1, U5.P6, U5.P7
GND5: C11.2, C12.2, J16.1, J18.1, LED5.1, R35.1, TP24.1, U6.P6, U6.P7
GND6: C13.2, C14.2, J19.1, J21.1, LED6.1, R41.1, TP28.1, U7.P6, U7.P7
GND7: C15.2, C16.2, J22.1, J24.1, LED7.1, R47.1, TP32.1, U8.P6, U8.P7
GND8: C17.2, C18.2, J25.1, J27.1, LED8.1, R53.1, TP36.1, U9.P6, U9.P7
GND9: C19.2, C20.2, J28.1, J30.1, LED9.1, R59.1, TP40.1, U10.P6, U10.P7
GND10: C21.2, C22.2, J31.1, J33.1, LED10.1, R65.1, TP44.1, U11.P6, U11.P7
GND11: C23.2, C24.2, J34.1, J36.1, LED11.1, R71.1, TP48.1, U12.P6, U12.P7
GND12: C25.2, C26.2, J37.1, J39.1, LED12.1, R77.1, TP52.1, U13.P6, U13.P7
GND13: C27.2, C28.2, J40.1, J42.1, LED13.1, R83.1, TP56.1, U14.P6, U14.P7
GND14: C29.2, C30.2, J43.1, J45.1, LED14.1, R89.1, TP60.1, U15.P6, U15.P7
GND15: C31.2, C32.2, J46.1, J48.1, LED15.1, R95.1, TP64.1, U16.P6, U16.P7
GND16: C33.2, C34.2, J49.1, J51.1, LED16.1, R101.1, TP68.1, U17.P6, U17.P7
GND17: C35.2, C36.2, J52.1, J54.1, LED17.1, R107.1, TP72.1, U18.P6, U18.P7
GND18: C37.2, C38.2, J55.1, J57.1, LED18.1, R113.1, TP76.1, U19.P6, U19.P7
GND19: C39.2, C40.2, J58.1, J60.1, LED19.1, R119.1, TP80.1, U20.P6, U20.P7
GND20: C41.2, C42.2, J61.1, J63.1, LED20.1, R125.1, TP84.1, U21.P6, U21.P7
GND21: C43.2, C44.2, J64.1, J66.1, LED21.1, R131.1, TP88.1, U22.P6, U22.P7
GND22: C45.2, C46.2, J67.1, J69.1, LED22.1, R137.1, TP92.1, U23.P6, U23.P7
GND23: C47.2, C48.2, J70.1, J72.1, LED23.1, R143.1, TP96.1, U24.P6, U24.P7
GND24: C49.2, C50.2, J73.1, J75.1, LED24.1, R149.1, TP100.1, U25.P6, U25.P7
GND25: C51.2, C52.2, J76.1, J78.1, LED25.1, R155.1, TP104.1, U26.P6, U26.P7
GND26: C53.2, C54.2, J79.1, J81.1, LED26.1, R161.1, TP108.1, U27.P6, U27.P7
GND27: C55.2, C56.2, J82.1, J84.1, LED27.1, R167.1, TP112.1, U28.P6, U28.P7
GND28: C57.2, C58.2, J85.1, J87.1, LED28.1, R173.1, TP116.1, U29.P6, U29.P7
GND29: C59.2, C60.2, J88.1, J90.1, LED29.1, R179.1, TP120.1, U30.P6, U30.P7
GND30: C61.2, C62.2, J91.1, J93.1, LED30.1, R185.1, TP124.1, U31.P6, U31.P7
GND31: C63.2, C64.2, J94.1, J96.1, LED31.1, R191.1, TP128.1, U32.P6, U32.P7
GND32: C65.2, C66.2, J97.1, J99.1, LED32.1, R197.1, TP132.1, U33.P6, U33.P7
GND33: C67.2, C68.2, J100.1, J102.1, LED33.1, R203.1, TP136.1, U34.P6, U34.P7
GND34: C69.2, C70.2, J103.1, J105.1, LED34.1, R209.1, TP140.1, U35.P6, U35.P7
GND35: C71.2, C72.2, J106.1, J108.1, LED35.1, R215.1, TP144.1, U36.P6, U36.P7
GND36: C73.2, C74.2, J109.1, J111.1, LED36.1, R221.1, TP148.1, U37.P6, U37.P7
GND37: C75.2, C76.2, J112.1, J114.1, LED37.1, R227.1, TP152.1, U38.P6, U38.P7
GND38: C77.2, C78.2, J115.1, J117.1, LED38.1, R233.1, TP156.1, U39.P6, U39.P7
GND39: C79.2, C80.2, J118.1, J120.1, LED39.1, R239.1, TP160.1, U40.P6, U40.P7
GND40: C81.2, C82.2, J121.1, J123.1, LED40.1, R245.1, TP164.1, U41.P6, U41.P7
GND41: C83.2, C84.2, J124.1, J126.1, LED41.1, R251.1, TP168.1, U42.P6, U42.P7
GND42: C85.2, C86.2, J127.1, J129.1, LED42.1, R257.1, TP172.1, U43.P6, U43.P7
GND43: C87.2, C88.2, J130.1, J132.1, LED43.1, R263.1, TP176.1, U44.P6, U44.P7
GND44: C89.2, C90.2, J133.1, J135.1, LED44.1, R269.1, TP180.1, U45.P6, U45.P7
GND45: C91.2, C92.2, J136.1, J138.1, LED45.1, R275.1, TP184.1, U46.P6, U46.P7
GND46: C93.2, C94.2, J139.1, J141.1, LED46.1, R281.1, TP188.1, U47.P6, U47.P7
GND47: C95.2, C96.2, J142.1, J144.1, LED47.1, R287.1, TP192.1, U48.P6, U48.P7
GND48: C97.2, C98.2, J145.1, J147.1, LED48.1, R293.1, TP196.1, U49.P6, U49.P7
GND49: C99.2, C100.2, J148.1, J150.1, LED49.1, R299.1, TP200.1, U50.P6, U50.P7
GND50: C101.2, C102.2, J151.1, J153.1, LED50.1, R305.1, TP204.1, U51.P6, U51.P7
GND51: C103.2, C104.2, J154.1, J156.1, LED51.1, R311.1, TP208.1, U52.P6, U52.P7
GND52: C105.2, C106.2, J157.1, J159.1, LED52.1, R317.1, TP212.1, U53.P6, U53.P7
GND53: C107.2, C108.2, J160.1, J162.1, LED53.1, R323.1, TP216.1, U54.P6, U54.P7
GND54: C109.2, C110.2, J163.1, J165.1, LED54.1, R329.1, TP220.1, U55.P6, U55.P7
GND55: C111.2, C112.2, J166.1, J168.1, LED55.1, R335.1, TP224.1, U56.P6, U56.P7
GND56: C113.2, C114.2, J169.1, J171.1, LED56.1, R341.1, TP228.1, U57.P6, U57.P7
GND57: C115.2, C116.2, J172.1, J174.1, LED57.1, R347.1, TP232.1, U58.P6, U58.P7
GND58: C117.2, C118.2, J175.1, J177.1, LED58.1, R353.1, TP236.1, U59.P6, U59.P7
GND59: C119.2, C120.2, J178.1, J180.1, LED59.1, R359.1, TP240.1, U60.P6, U60.P7
GND60: C121.2, C122.2, J181.1, J183.1, LED60.1, R365.1, TP244.1, U61.P6, U61.P7
GND61: C123.2, C124.2, J184.1, J186.1, LED61.1, R371.1, TP248.1, U62.P6, U62.P7
GND62: C125.2, C126.2, J187.1, J189.1, LED62.1, R377.1, TP252.1, U63.P6, U63.P7
GND63: C127.2, C128.2, J190.1, J192.1, LED63.1, R383.1, TP256.1, U64.P6, U64.P7
INT1: J3.1, U1.P4
INT2: J5.1, U2.P4
INT3: J8.1, U3.P4
INT4: J11.1, U4.P4
INT5: J14.1, U5.P4
INT6: J17.1, U6.P4
INT7: J20.1, U7.P4
INT8: J23.1, U8.P4
INT9: J26.1, U9.P4
INT10: J29.1, U10.P4
INT11: J32.1, U11.P4
INT12: J35.1, U12.P4
INT13: J38.1, U13.P4
INT14: J41.1, U14.P4
INT15: J44.1, U15.P4
INT16: J47.1, U16.P4
INT17: J50.1, U17.P4
INT18: J53.1, U18.P4
INT19: J56.1, U19.P4
INT20: J59.1, U20.P4
INT21: J62.1, U21.P4
INT22: J65.1, U22.P4
INT23: J68.1, U23.P4
INT24: J71.1, U24.P4
INT25: J74.1, U25.P4
INT26: J77.1, U26.P4
INT27: J80.1, U27.P4
INT28: J83.1, U28.P4
INT29: J86.1, U29.P4
INT30: J89.1, U30.P4
INT31: J92.1, U31.P4
INT32: J95.1, U32.P4
INT33: J98.1, U33.P4
INT34: J101.1, U34.P4
INT35: J104.1, U35.P4
INT36: J107.1, U36.P4
INT37: J110.1, U37.P4
INT38: J113.1, U38.P4
INT39: J116.1, U39.P4
INT40: J119.1, U40.P4
INT41: J122.1, U41.P4
INT42: J125.1, U42.P4
INT43: J128.1, U43.P4
INT44: J131.1, U44.P4
INT45: J134.1, U45.P4
INT46: J137.1, U46.P4
INT47: J140.1, U47.P4
INT48: J143.1, U48.P4
INT49: J146.1, U49.P4
INT50: J149.1, U50.P4
INT51: J152.1, U51.P4
INT52: J155.1, U52.P4
INT53: J158.1, U53.P4
INT54: J161.1, U54.P4
INT55: J164.1, U55.P4
INT56: J167.1, U56.P4
INT57: J170.1, U57.P4
INT58: J173.1, U58.P4
INT59: J176.1, U59.P4
INT60: J179.1, U60.P4
INT61: J182.1, U61.P4
INT62: J185.1, U62.P4
INT63: J188.1, U63.P4
INT64: J191.1, U64.P4
unnamed: ADDR.3, R5.1
unnamed: D1.A, R4.1
unnamed: D1.C, LED.2
unnamed: R3.1, U1.P12
unnamed: I2C_PU.1, R1.2
unnamed: I2C_PU.3, R2.2
unnamed: ADDR.1, R6.2
unnamed: I2C_PU1.1, R7.2
unnamed: I2C_PU1.3, R8.2
unnamed: D2.A, R9.1
unnamed: D2.C, LED1.2
unnamed: ADDR1.3, R10.1
unnamed: ADDR1.1, R11.2
unnamed: R12.1, U2.P12
unnamed: I2C_PU2.1, R13.2
unnamed: I2C_PU2.3, R14.2
unnamed: D3.A, R15.1
unnamed: D3.C, LED2.2
unnamed: ADDR2.3, R16.1
unnamed: ADDR2.1, R17.2
unnamed: R18.1, U3.P12
unnamed: I2C_PU3.1, R19.2
unnamed: I2C_PU3.3, R20.2
unnamed: D4.A, R21.1
unnamed: D4.C, LED3.2
unnamed: ADDR3.3, R22.1
unnamed: ADDR3.1, R23.2
unnamed: R24.1, U4.P12
unnamed: I2C_PU4.1, R25.2
unnamed: I2C_PU4.3, R26.2
unnamed: D5.A, R27.1
unnamed: D5.C, LED4.2
unnamed: ADDR4.3, R28.1
unnamed: ADDR4.1, R29.2
unnamed: R30.1, U5.P12
unnamed: I2C_PU5.1, R31.2
unnamed: I2C_PU5.3, R32.2
unnamed: D6.A, R33.1
unnamed: D6.C, LED5.2
unnamed: ADDR5.3, R34.1
unnamed: ADDR5.1, R35.2
unnamed: R36.1, U6.P12
unnamed: I2C_PU6.1, R37.2
unnamed: I2C_PU6.3, R38.2
unnamed: D7.A, R39.1
unnamed: D7.C, LED6.2
unnamed: ADDR6.3, R40.1
unnamed: ADDR6.1, R41.2
unnamed: R42.1, U7.P12
unnamed: I2C_PU7.1, R43.2
unnamed: I2C_PU7.3, R44.2
unnamed: D8.A, R45.1
unnamed: D8.C, LED7.2
unnamed: ADDR7.3, R46.1
unnamed: ADDR7.1, R47.2
unnamed: R48.1, U8.P12
unnamed: I2C_PU8.1, R49.2
unnamed: I2C_PU8.3, R50.2
unnamed: D9.A, R51.1
unnamed: D9.C, LED8.2
unnamed: ADDR8.3, R52.1
unnamed: ADDR8.1, R53.2
unnamed: R54.1, U9.P12
unnamed: I2C_PU9.1, R55.2
unnamed: I2C_PU9.3, R56.2
unnamed: D10.A, R57.1
unnamed: D10.C, LED9.2
unnamed: ADDR9.3, R58.1
unnamed: ADDR9.1, R59.2
unnamed: R60.1, U10.P12
unnamed: I2C_PU10.1, R61.2
unnamed: I2C_PU10.3, R62.2
unnamed: D11.A, R63.1
unnamed: D11.C, LED10.2
unnamed: ADDR10.3, R64.1
unnamed: ADDR10.1, R65.2
unnamed: R66.1, U11.P12
unnamed: I2C_PU11.1, R67.2
unnamed: I2C_PU11.3, R68.2
unnamed: D12.A, R69.1
unnamed: D12.C, LED11.2
unnamed: ADDR11.3, R70.1
unnamed: ADDR11.1, R71.2
unnamed: R72.1, U12.P12
unnamed: I2C_PU12.1, R73.2
unnamed: I2C_PU12.3, R74.2
unnamed: D13.A, R75.1
unnamed: D13.C, LED12.2
unnamed: ADDR12.3, R76.1
unnamed: ADDR12.1, R77.2
unnamed: R78.1, U13.P12
unnamed: I2C_PU13.1, R79.2
unnamed: I2C_PU13.3, R80.2
unnamed: D14.A, R81.1
unnamed: D14.C, LED13.2
unnamed: ADDR13.3, R82.1
unnamed: ADDR13.1, R83.2
unnamed: R84.1, U14.P12
unnamed: I2C_PU14.1, R85.2
unnamed: I2C_PU14.3, R86.2
unnamed: D15.A, R87.1
unnamed: D15.C, LED14.2
unnamed: ADDR14.3, R88.1
unnamed: ADDR14.1, R89.2
unnamed: R90.1, U15.P12
unnamed: I2C_PU15.1, R91.2
unnamed: I2C_PU15.3, R92.2
unnamed: D16.A, R93.1
unnamed: D16.C, LED15.2
unnamed: ADDR15.3, R94.1
unnamed: ADDR15.1, R95.2
unnamed: R96.1, U16.P12
unnamed: I2C_PU16.1, R97.2
unnamed: I2C_PU16.3, R98.2
unnamed: D17.A, R99.1
unnamed: D17.C, LED16.2
unnamed: ADDR16.3, R100.1
unnamed: ADDR16.1, R101.2
unnamed: R102.1, U17.P12
unnamed: I2C_PU17.1, R103.2
unnamed: I2C_PU17.3, R104.2
unnamed: D18.A, R105.1
unnamed: D18.C, LED17.2
unnamed: ADDR17.3, R106.1
unnamed: ADDR17.1, R107.2
unnamed: R108.1, U18.P12
unnamed: I2C_PU18.1, R109.2
unnamed: I2C_PU18.3, R110.2
unnamed: D19.A, R111.1
unnamed: D19.C, LED18.2
unnamed: ADDR18.3, R112.1
unnamed: ADDR18.1, R113.2
unnamed: R114.1, U19.P12
unnamed: I2C_PU19.1, R115.2
unnamed: I2C_PU19.3, R116.2
unnamed: D20.A, R117.1
unnamed: D20.C, LED19.2
unnamed: ADDR19.3, R118.1
unnamed: ADDR19.1, R119.2
unnamed: R120.1, U20.P12
unnamed: I2C_PU20.1, R121.2
unnamed: I2C_PU20.3, R122.2
unnamed: D21.A, R123.1
unnamed: D21.C, LED20.2
unnamed: ADDR20.3, R124.1
unnamed: ADDR20.1, R125.2
unnamed: R126.1, U21.P12
unnamed: I2C_PU21.1, R127.2
unnamed: I2C_PU21.3, R128.2
unnamed: D22.A, R129.1
unnamed: D22.C, LED21.2
unnamed: ADDR21.3, R130.1
unnamed: ADDR21.1, R131.2
unnamed: R132.1, U22.P12
unnamed: I2C_PU22.1, R133.2
unnamed: I2C_PU22.3, R134.2
unnamed: D23.A, R135.1
unnamed: D23.C, LED22.2
unnamed: ADDR22.3, R136.1
unnamed: ADDR22.1, R137.2
unnamed: R138.1, U23.P12
unnamed: I2C_PU23.1, R139.2
unnamed: I2C_PU23.3, R140.2
unnamed: D24.A, R141.1
unnamed: D24.C, LED23.2
unnamed: ADDR23.3, R142.1
unnamed: ADDR23.1, R143.2
unnamed: R144.1, U24.P12
unnamed: I2C_PU24.1, R145.2
unnamed: I2C_PU24.3, R146.2
unnamed: D25.A, R147.1
unnamed: D25.C, LED24.2
unnamed: ADDR24.3, R148.1
unnamed: ADDR24.1, R149.2
unnamed: R150.1, U25.P12
unnamed: I2C_PU25.1, R151.2
unnamed: I2C_PU25.3, R152.2
unnamed: D26.A, R153.1
unnamed: D26.C, LED25.2
unnamed: ADDR25.3, R154.1
unnamed: ADDR25.1, R155.2
unnamed: R156.1, U26.P12
unnamed: I2C_PU26.1, R157.2
unnamed: I2C_PU26.3, R158.2
unnamed: D27.A, R159.1
unnamed: D27.C, LED26.2
unnamed: ADDR26.3, R160.1
unnamed: ADDR26.1, R161.2
unnamed: R162.1, U27.P12
unnamed: I2C_PU27.1, R163.2
unnamed: I2C_PU27.3, R164.2
unnamed: D28.A, R165.1
unnamed: D28.C, LED27.2
unnamed: ADDR27.3, R166.1
unnamed: ADDR27.1, R167.2
unnamed: R168.1, U28.P12
unnamed: I2C_PU28.1, R169.2
unnamed: I2C_PU28.3, R170.2
unnamed: D29.A, R171.1
unnamed: D29.C, LED28.2
unnamed: ADDR28.3, R172.1
unnamed: ADDR28.1, R173.2
unnamed: R174.1, U29.P12
unnamed: I2C_PU29.1, R175.2
unnamed: I2C_PU29.3, R176.2
unnamed: D30.A, R177.1
unnamed: D30.C, LED29.2
unnamed: ADDR29.3, R178.1
unnamed: ADDR29.1, R179.2
unnamed: R180.1, U30.P12
unnamed: I2C_PU30.1, R181.2
unnamed: I2C_PU30.3, R182.2
unnamed: D31.A, R183.1
unnamed: D31.C, LED30.2
unnamed: ADDR30.3, R184.1
unnamed: ADDR30.1, R185.2
unnamed: R186.1, U31.P12
unnamed: I2C_PU31.1, R187.2
unnamed: I2C_PU31.3, R188.2
unnamed: D32.A, R189.1
unnamed: D32.C, LED31.2
unnamed: ADDR31.3, R190.1
unnamed: ADDR31.1, R191.2
unnamed: R192.1, U32.P12
unnamed: I2C_PU32.1, R193.2
unnamed: I2C_PU32.3, R194.2
unnamed: D33.A, R195.1
unnamed: D33.C, LED32.2
unnamed: ADDR32.3, R196.1
unnamed: ADDR32.1, R197.2
unnamed: R198.1, U33.P12
unnamed: I2C_PU33.1, R199.2
unnamed: I2C_PU33.3, R200.2
unnamed: D34.A, R201.1
unnamed: D34.C, LED33.2
unnamed: ADDR33.3, R202.1
unnamed: ADDR33.1, R203.2
unnamed: R204.1, U34.P12
unnamed: I2C_PU34.1, R205.2
unnamed: I2C_PU34.3, R206.2
unnamed: D35.A, R207.1
unnamed: D35.C, LED34.2
unnamed: ADDR34.3, R208.1
unnamed: ADDR34.1, R209.2
unnamed: R210.1, U35.P12
unnamed: I2C_PU35.1, R211.2
unnamed: I2C_PU35.3, R212.2
unnamed: D36.A, R213.1
unnamed: D36.C, LED35.2
unnamed: ADDR35.3, R214.1
unnamed: ADDR35.1, R215.2
unnamed: R216.1, U36.P12
unnamed: I2C_PU36.1, R217.2
unnamed: I2C_PU36.3, R218.2
unnamed: D37.A, R219.1
unnamed: D37.C, LED36.2
unnamed: ADDR36.3, R220.1
unnamed: ADDR36.1, R221.2
unnamed: R222.1, U37.P12
unnamed: I2C_PU37.1, R223.2
unnamed: I2C_PU37.3, R224.2
unnamed: D38.A, R225.1
unnamed: D38.C, LED37.2
unnamed: ADDR37.3, R226.1
unnamed: ADDR37.1, R227.2
unnamed: R228.1, U38.P12
unnamed: I2C_PU38.1, R229.2
unnamed: I2C_PU38.3, R230.2
unnamed: D39.A, R231.1
unnamed: D39.C, LED38.2
unnamed: ADDR38.3, R232.1
unnamed: ADDR38.1, R233.2
unnamed: R234.1, U39.P12
unnamed: I2C_PU39.1, R235.2
unnamed: I2C_PU39.3, R236.2
unnamed: D40.A, R237.1
unnamed: D40.C, LED39.2
unnamed: ADDR39.3, R238.1
unnamed: ADDR39.1, R239.2
unnamed: R240.1, U40.P12
unnamed: I2C_PU40.1, R241.2
unnamed: I2C_PU40.3, R242.2
unnamed: D41.A, R243.1
unnamed: D41.C, LED40.2
unnamed: ADDR40.3, R244.1
unnamed: ADDR40.1, R245.2
unnamed: R246.1, U41.P12
unnamed: I2C_PU41.1, R247.2
unnamed: I2C_PU41.3, R248.2
unnamed: D42.A, R249.1
unnamed: D42.C, LED41.2
unnamed: ADDR41.3, R250.1
unnamed: ADDR41.1, R251.2
unnamed: R252.1, U42.P12
unnamed: I2C_PU42.1, R253.2
unnamed: I2C_PU42.3, R254.2
unnamed: D43.A, R255.1
unnamed: D43.C, LED42.2
unnamed: ADDR42.3, R256.1
unnamed: ADDR42.1, R257.2
unnamed: R258.1, U43.P12
unnamed: I2C_PU43.1, R259.2
unnamed: I2C_PU43.3, R260.2
unnamed: D44.A, R261.1
unnamed: D44.C, LED43.2
unnamed: ADDR43.3, R262.1
unnamed: ADDR43.1, R263.2
unnamed: R264.1, U44.P12
unnamed: I2C_PU44.1, R265.2
unnamed: I2C_PU44.3, R266.2
unnamed: D45.A, R267.1
unnamed: D45.C, LED44.2
unnamed: ADDR44.3, R268.1
unnamed: ADDR44.1, R269.2
unnamed: R270.1, U45.P12
unnamed: I2C_PU45.1, R271.2
unnamed: I2C_PU45.3, R272.2
unnamed: D46.A, R273.1
unnamed: D46.C, LED45.2
unnamed: ADDR45.3, R274.1
unnamed: ADDR45.1, R275.2
unnamed: R276.1, U46.P12
unnamed: I2C_PU46.1, R277.2
unnamed: I2C_PU46.3, R278.2
unnamed: D47.A, R279.1
unnamed: D47.C, LED46.2
unnamed: ADDR46.3, R280.1
unnamed: ADDR46.1, R281.2
unnamed: R282.1, U47.P12
unnamed: I2C_PU47.1, R283.2
unnamed: I2C_PU47.3, R284.2
unnamed: D48.A, R285.1
unnamed: D48.C, LED47.2
unnamed: ADDR47.3, R286.1
unnamed: ADDR47.1, R287.2
unnamed: R288.1, U48.P12
unnamed: I2C_PU48.1, R289.2
unnamed: I2C_PU48.3, R290.2
unnamed: D49.A, R291.1
unnamed: D49.C, LED48.2
unnamed: ADDR48.3, R292.1
unnamed: ADDR48.1, R293.2
unnamed: R294.1, U49.P12
unnamed: I2C_PU49.1, R295.2
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
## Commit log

2022-02-28 Adds documentation, copies over other 6DoF For basic shell of a design
2022-03-01 Adds ISM330DHCX part
2022-03-01 Fixes IC name
2022-04-01 Updates notes in schematic (schematic done)
    * Adds 10k to ground to address selection just in case someone bridges the entire three way jumper
2022-04-04 Completes routing, had to swap SDO and CS for ease of routing
2022-04-04 Adds labels, fixes wonky box in schematic
2022-04-04 Routes most of the micro board - I need to make space for lables on the underside.
2022-04-04 Moves the i2c jumper
2022-04-04 Moves SDI_Aux and SDO_Aux jumpers to topside
2022-04-04 Moves fiducials back, cleans up some traces
2022-04-04 Adds labels to Mini
2022-04-04 Adds Qwiic Micro
    * Given the nature of the design I was not able to get the board any smaller than a Qwiic mini, so I didn't bother routing it.
2022-04-04 Adds a save point for Qwiic Micro - Revert here if removing SPI is not
    the way.
2022-04-04 Removes Auxiliary pins to make the Qwiic Micro as Micro as possible
2022-04-04 Adds measures
2022-04-04 Puts the three designs into folders
2022-04-04 Updates labels on 1x1 to new SPI nomenclature,
    * moves pin1 indicator on IC closer to IC
2022-04-04 Updates labels on Qwiic Micro, Updates IC on Qwiic Micro and Micro
2022-04-06 Resizes and reroutes the Qwiic Micro board
2022-04-06 Extends board to 0.75", adds better labels, adds 0402 LED to design
2022-04-06 Moves some vias, fixes "x", "y", and "z" on axes, fixes some schematic typos
2022-04-06 Fixes labels, realigns the SDX jumper on top
2022-04-06 Moves resistor so that PWR silk is close to the LED
    * Fixes some trace bends
2022-04-07 small adjustments
2022-04-08 Adds a new Qwiic Micro
2022-04-08 Cams every design
2022-04-13 Fixes axes on bottom side incorrectly labeling the Z axis
2022-04-13 Updates the PROD_ID
2022-04-14 Fixes clearance issue with vias near 3v3 trace
2022-04-14 Removes pin numbers from ISM330DHCX symbol
    *Updates all designs to include the change which also included an update to the PROD_ID
2022-04-18 Moves CS to top of symbol, moves VDD_IO to make space for SDA pin
2022-05-31 Removes unused size
2022-05-31 Removes proto gerbers, renames Qwiic_micro_alternate -> Qwiic_micro
2022-05-31 Fixes swapped silk on PICO and CS headers, changes to v10, adds "default" text to default address
2022-05-31 Moves test points to their designated areas, increases the size of most of the silk
    * Moves to v10
2022-05-31 Adds all the measures anyone could want
2022-06-01 adds 10k pullup on CS
2022-06-02 Fixes silk for X-axis, changes tails on INT and GND silk
2022-06-02 Fixes some DRC errors
2022-06-02 Updates INT2 to rounded, and changes INT text on Micro to INT1
2022-06-03 Adds a via, adds some clearer text to the schematic
2022-06-03 Adds some text about i2c address and PTH connectors
2022-06-03 Removes old prototype gerbers and the "Micro" version
2022-06-03 Adds panel for Qwiic board
2022-06-03 Adds Qwiic Micro production files, moves them into their own folders
2022-06-08 Renames production files to include version number, updates 0402 RED LED with one that has PROD_ID
2022-08-25 Removes extraneous parts library
